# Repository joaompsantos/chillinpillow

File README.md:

# ComfortLabs

## Chillin'Pillow

The **pillow** you wanted since the dawn of time!
**Chillin'Pillow** is a smart, not dumb at least, pilow. It's an amazing gadtget that well help you fall asleep and awake better. 

### Features
- Bluetooth Conectivity;
- Mobile App;
- Set vibration settings;
- Small eletronics package for maximum comfort;
- One week battery*;
- Usb Rechargeable;

### Documentation
Both docs and libs folders contain datasheets, manuals, reference guides and code libraries.

### Credits
We used some Libraries available online like the [SparkFun Eagle Libraries](https://github.com/sparkfun/SparkFun-Eagle-Libraries).

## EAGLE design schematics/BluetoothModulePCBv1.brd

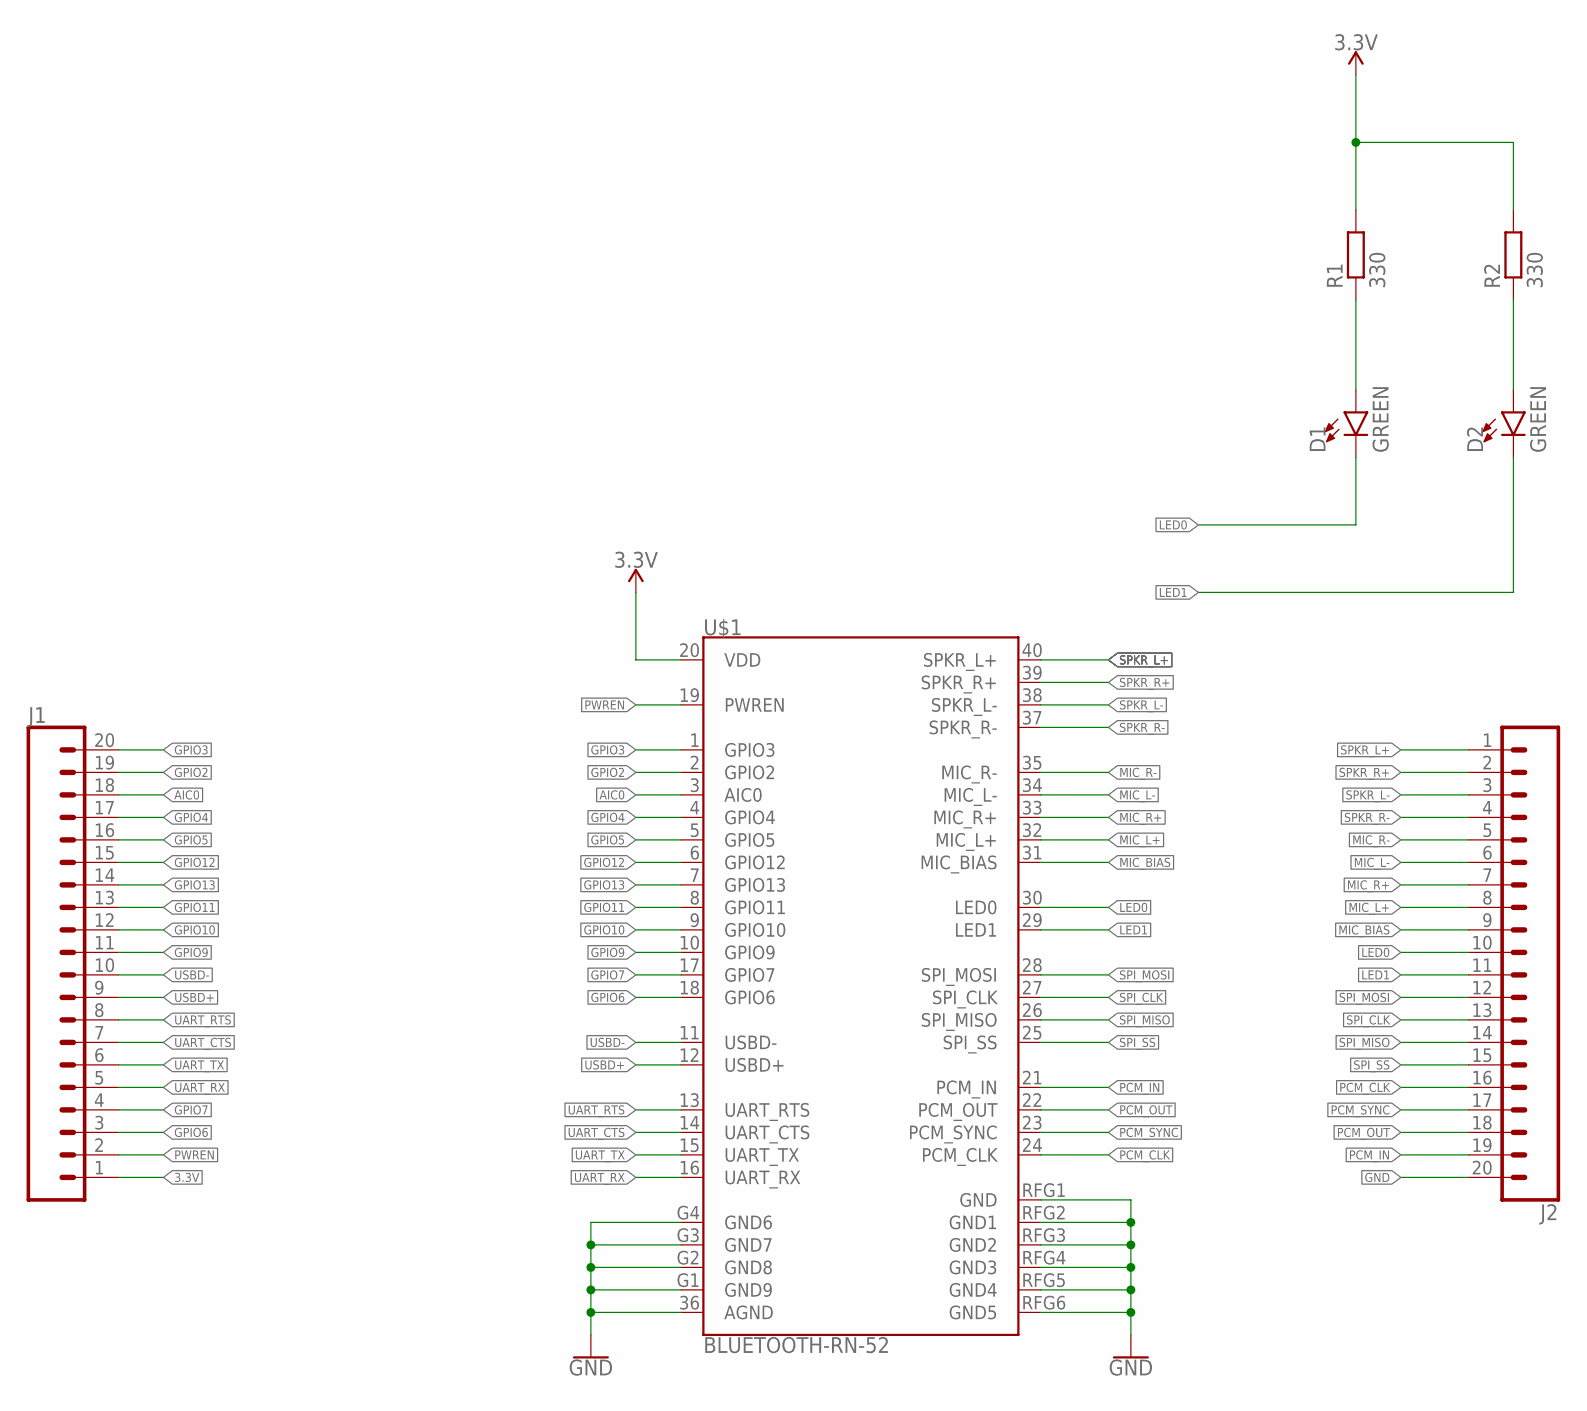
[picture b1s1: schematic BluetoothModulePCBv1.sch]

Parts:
D1, D2: GREEN; LED_3MM
J1, J2: CONN_20; 1X20
R1, R2: 330; 0204/7
U$1: BLUETOOTH-RN-52; RN-52

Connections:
3.3V: J1.1, R1.2, R2.2, U$1.20 (VDD)
AIC0: J1.18, U$1.3 (AIC0)
GND: J2.20, U$1.36 (AGND), U$1.G1 (GND9), U$1.G2 (GND8), U$1.G3 (GND7), U$1.G4 (GND6), U$1.RFG1 (GND), U$1.RFG2 (GND1), U$1.RFG3 (GND2), U$1.RFG4 (GND3), U$1.RFG5 (GND4), U$1.RFG6 (GND5)
GPIO2: J1.19, U$1.2 (GPIO2)
GPIO3: J1.20, U$1.1 (GPIO3)
GPIO4: J1.17, U$1.4 (GPIO4)
GPIO5: J1.16, U$1.5 (GPIO5)
GPIO6: J1.3, U$1.18 (GPIO6)
GPIO7: J1.4, U$1.17 (GPIO7)
GPIO9: J1.11, U$1.10 (GPIO9)
GPIO10: J1.12, U$1.9 (GPIO10)
GPIO11: J1.13, U$1.8 (GPIO11)
GPIO12: J1.15, U$1.6 (GPIO12)
GPIO13: J1.14, U$1.7 (GPIO13)
LED0: D1.K (C), J2.10, U$1.30 (LED0)
LED1: D2.K (C), J2.11, U$1.29 (LED1)
MIC_BIAS: J2.9, U$1.31 (MIC_BIAS)
MIC_L+: J2.8, U$1.32 (MIC_L+)
MIC_L-: J2.6, U$1.34 (MIC_L-)
MIC_R+: J2.7, U$1.33 (MIC_R+)
MIC_R-: J2.5, U$1.35 (MIC_R-)
unnamed: D1.A, R1.1
unnamed: D2.A, R2.1
PCM_CLK: J2.16, U$1.24 (PCM_CLK)
PCM_IN: J2.19, U$1.21 (PCM_IN)
PCM_OUT: J2.18, U$1.22 (PCM_OUT)
PCM_SYNC: J2.17, U$1.23 (PCM_SYNC)
PWREN: J1.2, U$1.19 (PWREN)
SPI_CLK: J2.13, U$1.27 (SPI_CLK)
SPI_MISO: J2.14, U$1.26 (SPI_MISO)
SPI_MOSI: J2.12, U$1.28 (SPI_MOSI)
SPI_SS: J2.15, U$1.25 (SPI_SS)
SPKR_L+: J2.1, U$1.40 (SPKR_L+)
SPKR_L-: J2.3, U$1.38 (SPKR_L-)
SPKR_R+: J2.2, U$1.39 (SPKR_R+)
SPKR_R-: J2.4, U$1.37 (SPKR_R-)
UART_CTS: J1.7, U$1.14 (UART_CTS)
UART_RTS: J1.8, U$1.13 (UART_RTS)
UART_RX: J1.5, U$1.16 (UART_RX)
UART_TX: J1.6, U$1.15 (UART_TX)
USBD+: J1.9, U$1.12 (USBD+)
USBD-: J1.10, U$1.11 (USBD-)

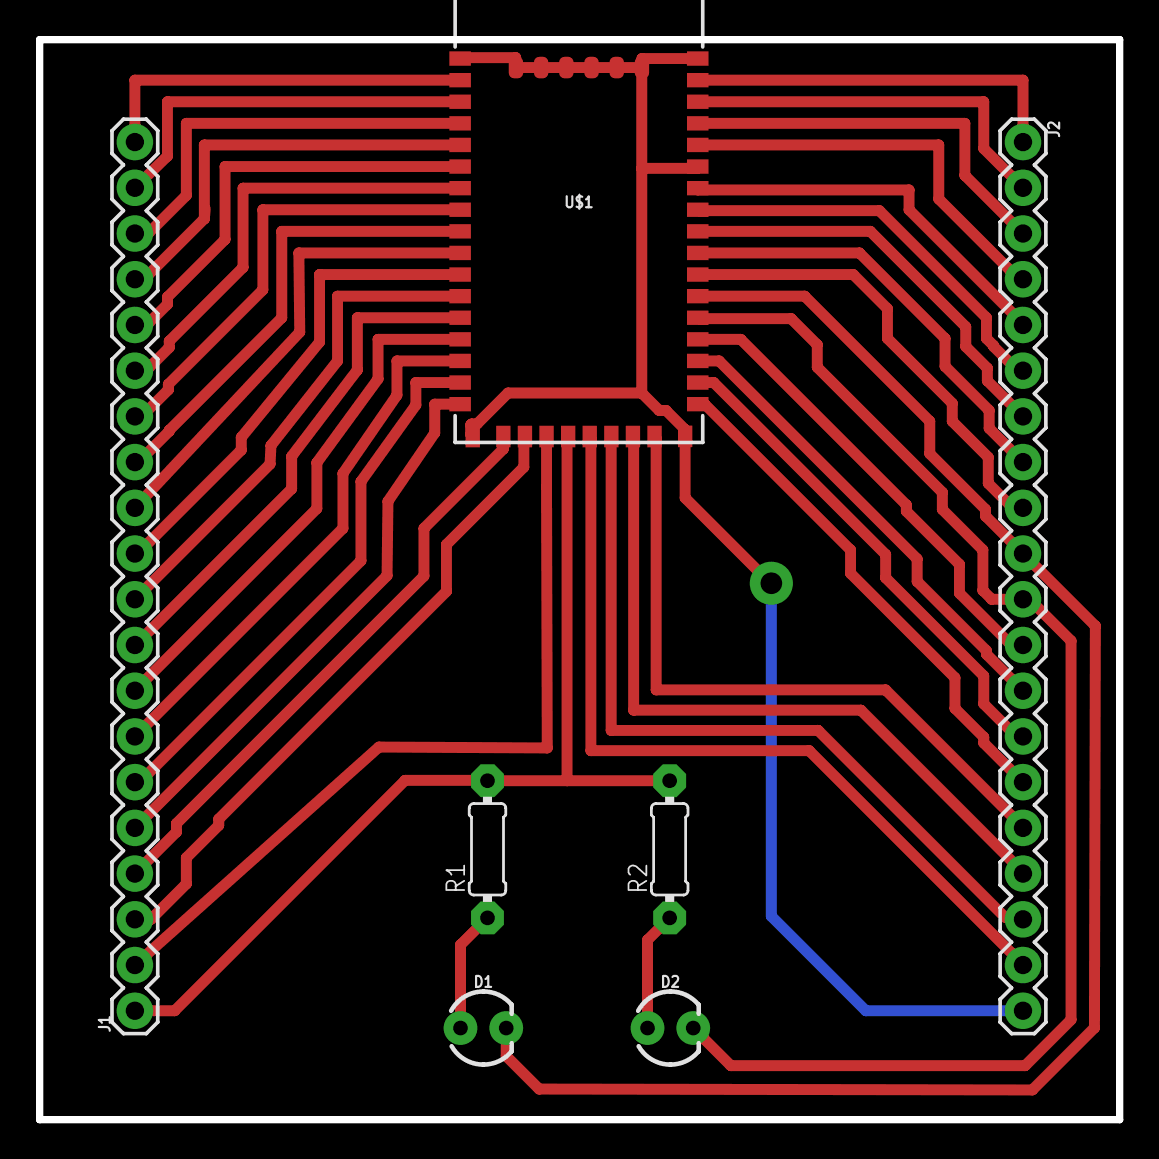
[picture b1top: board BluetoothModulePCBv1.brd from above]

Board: 2 copper layers, 60.0 x 60.0 mm, 7 parts (0 on the bottom side), 42 nets.

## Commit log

2017-06-13 Presented Version

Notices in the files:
parts and their libraries:
SparkFun-LED: Licensing: Creative Commons ShareAlike 4.0 International - https://creativecommons.org/licenses/by-sa/4.0
